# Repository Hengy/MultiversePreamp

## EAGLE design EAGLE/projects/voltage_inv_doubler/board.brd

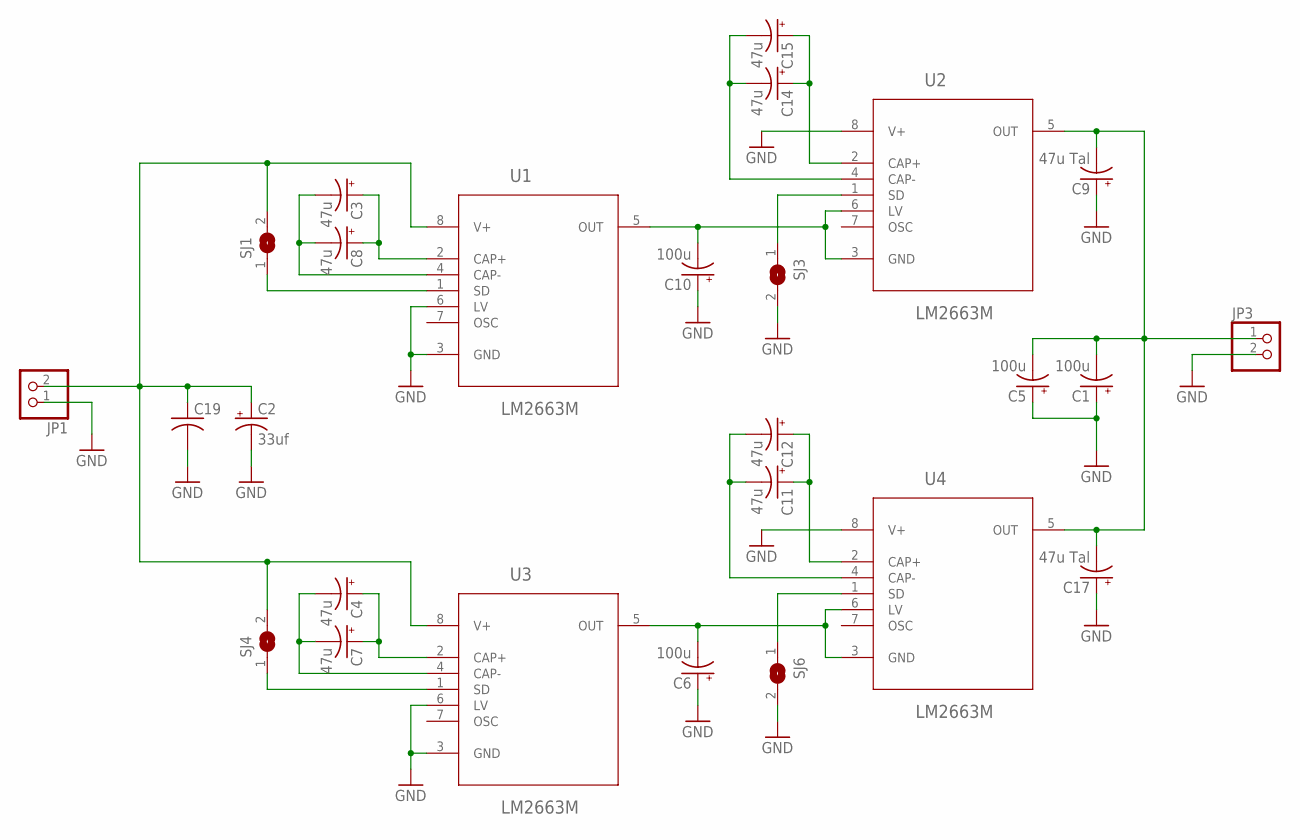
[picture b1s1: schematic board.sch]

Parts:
C1, C5: 100u; E2,5-6
C2: 33uf; E2-5
C3, C4, C7, C8, C11, C12, C14, C15: 47u; EIA3528-KIT
C6, C10: 100u; EIA7343
C9, C17: 47u Tal; EIA6032
C19: C-USC1206; C1206
JP1, JP3: PINHD-1X2; 1X02
SJ1, SJ3, SJ4, SJ6: SJ
U1, U2, U3, U4: LM2663M; SOIC127P620X175-8N

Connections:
GND: C1.+, C2.-, C5.+, C6.A (+), C9.P$1 (+), C10.A (+), C17.P$1 (+), C19.2, JP1.1, JP3.2, SJ3.2, SJ6.2, U1.3 (GND), U1.6 (LV), U2.8 (V+), U3.3 (GND), U3.6 (LV), U4.8 (V+)
unnamed: C2.+, C19.1, JP1.2, SJ1.2, SJ4.2, U1.8 (V+), U3.8 (V+)
unnamed: C14.A (+), C15.A (+), U2.2 (CAP+)
unnamed: SJ1.1, U1.1 (SD)
unnamed: SJ6.1, U4.1 (SD)
unnamed: C3.A (+), C8.A (+), U1.2 (CAP+)
unnamed: C3.C (-), C8.C (-), U1.4 (CAP-)
unnamed: C10.C (-), U1.5 (OUT), U2.3 (GND), U2.6 (LV)
unnamed: C14.C (-), C15.C (-), U2.4 (CAP-)
unnamed: C1.-, C5.-, C9.P$2 (-), C17.P$2 (-), JP3.1, U2.5 (OUT), U4.5 (OUT)
unnamed: SJ3.1, U2.1 (SD)
unnamed: C4.A (+), C7.A (+), U3.2 (CAP+)
unnamed: C4.C (-), C7.C (-), U3.4 (CAP-)
unnamed: C6.C (-), U3.5 (OUT), U4.3 (GND), U4.6 (LV)
unnamed: SJ4.1, U3.1 (SD)
unnamed: C11.A (+), C12.A (+), U4.2 (CAP+)
unnamed: C11.C (-), C12.C (-), U4.4 (CAP-)

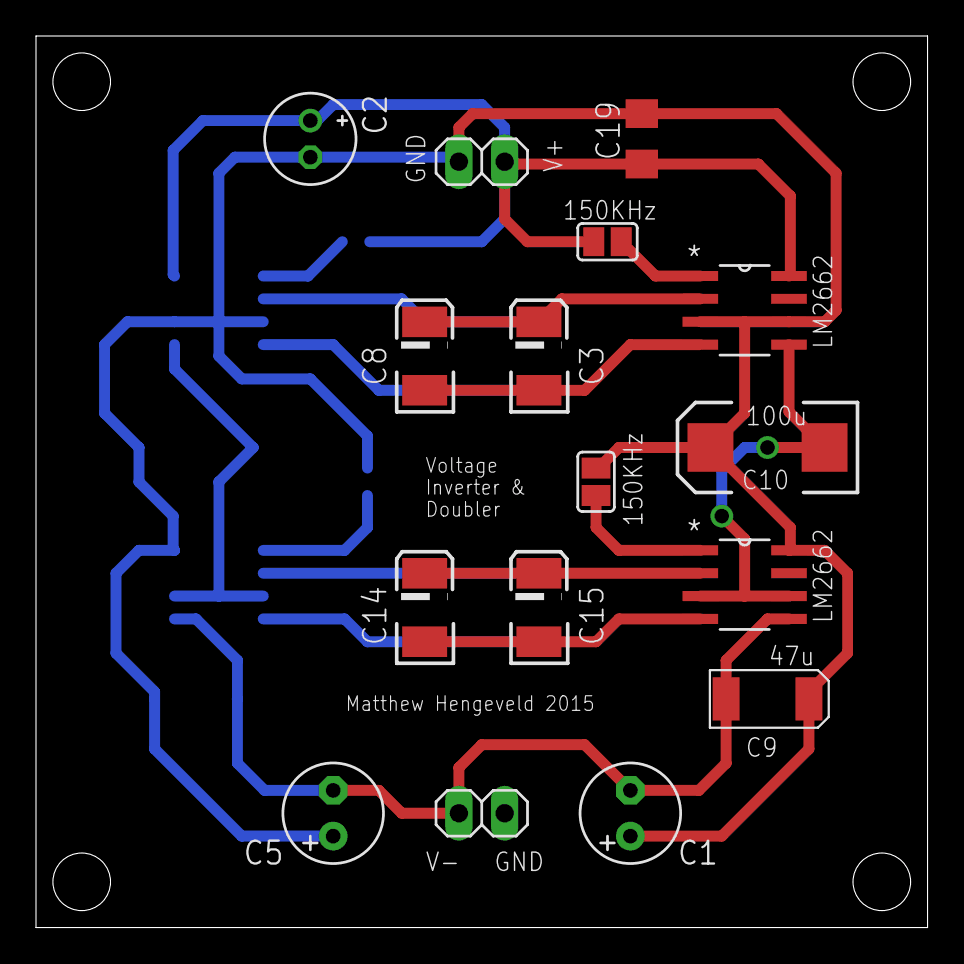
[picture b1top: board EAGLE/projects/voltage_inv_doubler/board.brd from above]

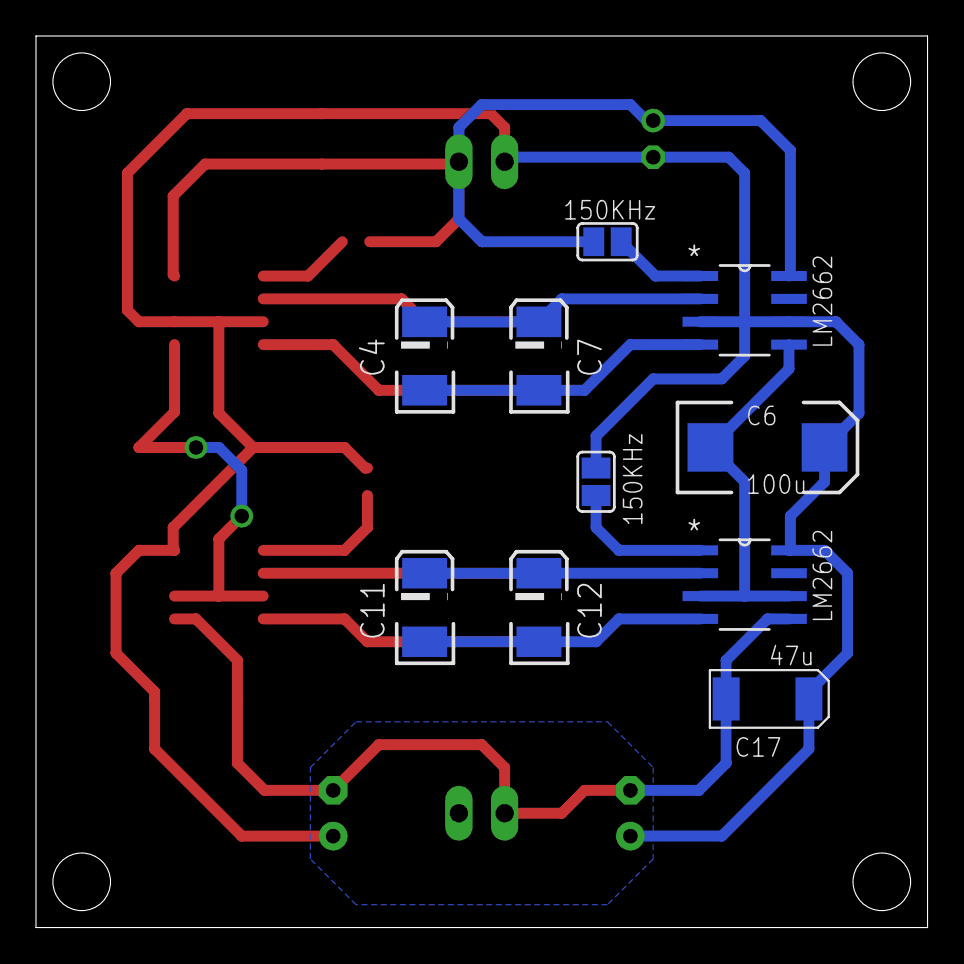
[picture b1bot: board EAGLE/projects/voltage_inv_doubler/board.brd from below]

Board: 2 copper layers, 49.5 x 49.5 mm, 26 parts (10 on the bottom side), 17 nets.

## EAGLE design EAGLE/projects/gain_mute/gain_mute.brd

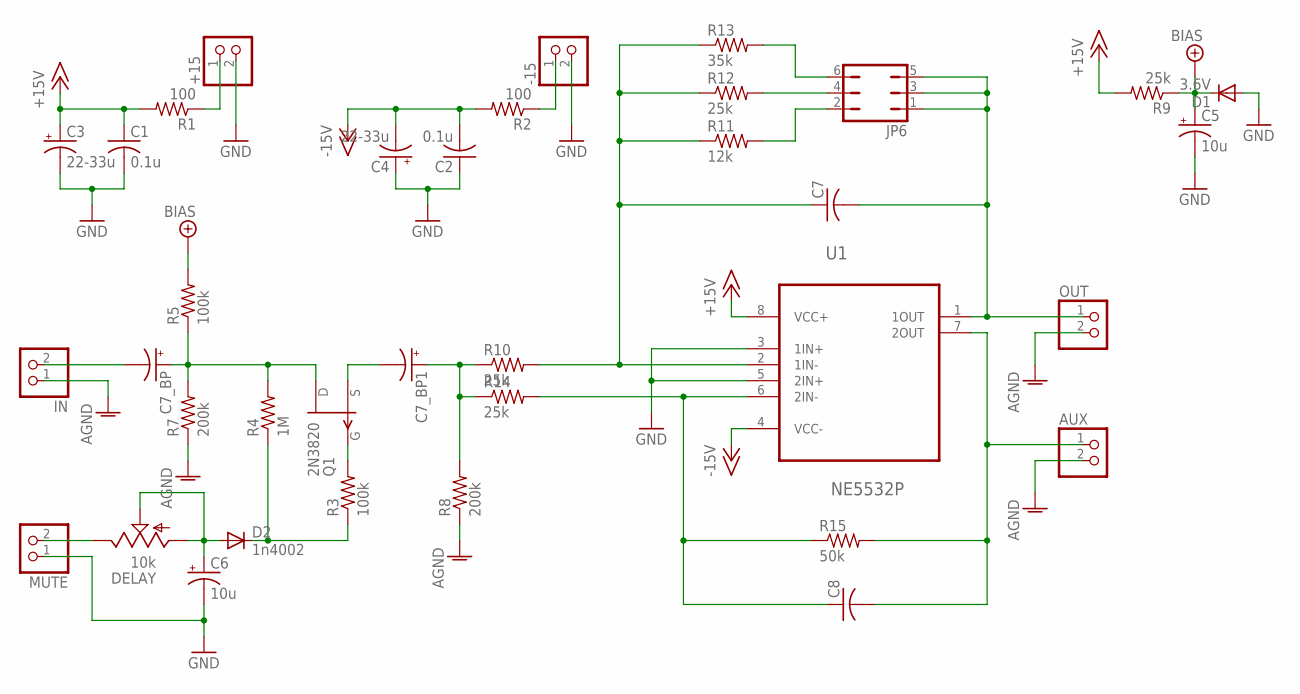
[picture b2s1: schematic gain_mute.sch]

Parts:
+15: PINHD-1X2; 1X02
-15: PINHD-1X2; 1X02
AUX: PINHD-1X2; 1X02
C1, C2: 0.1u; C1206
C3, C4: 22-33u; E2-5
C5, C6: 10u; E2-5
C7, C8: C-US050-024X044; C050-024X044
C7_BP, C7_BP1: CPOL-USE2.5-7; E2,5-7
D1: 3.6V; SOD123
D2: 1n4002; SOD123
DELAY: 10k; 3223J
IN: PINHD-1X2; 1X02
JP6: JP3Q
MUTE: PINHD-1X2; 1X02
OUT: PINHD-1X2; 1X02
Q1: 2N3820; TO92
R1, R2: 100; 0207/7
R3, R5: 100k; R1206
R4: 1M; R1206
R7, R8: 200k; R1206
R9: 25k; R1206
R10, R12, R14: 25k; 0207/7
R11: 12k; 0207/7
R13: 35k; 0207/7
R15: 50k; 0207/7
U1: NE5532P; DIP254P762X508-8

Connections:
+5V/2: C5.+, D1.C, R5.2, R9.1
+15V: C1.1, C3.+, R1.2, R9.2, U1.8 (VCC+)
-15V: C2.2, C4.-, R2.2, U1.4 (VCC-)
AGND: AUX.2, IN.1, OUT.2, R7.1, R8.1
GND: +15.2, -15.2, C1.2, C2.1, C3.-, C4.+, C5.-, C6.-, D1.A, MUTE.1, U1.3 (1IN+), U1.5 (2IN+)
unnamed: +15.1, R1.1
unnamed: C7_BP.-, IN.2
unnamed: DELAY.3 (E), MUTE.2
unnamed: -15.1, R2.1
unnamed: C7_BP.+, Q1.3 (D), R4.2, R5.1, R7.2
unnamed: C6.+, D2.A, DELAY.1 (A), DELAY.2 (S)
unnamed: D2.C, R3.1, R4.1
unnamed: Q1.2 (G), R3.2
unnamed: C7_BP1.-, Q1.1 (S)
unnamed: C7_BP1.+, R8.2, R10.1, R14.1
unnamed: C7.1, R10.2, R11.1, R12.1, R13.1, U1.2 (1IN-)
unnamed: JP6.4, R12.2
unnamed: JP6.6, R13.2
unnamed: JP6.2, R11.2
unnamed: C7.2, JP6.1, JP6.3, JP6.5, OUT.1, U1.1 (1OUT)
unnamed: AUX.1, C8.2, R15.2, U1.7 (2OUT)
unnamed: C8.1, R14.2, R15.1, U1.6 (2IN-)

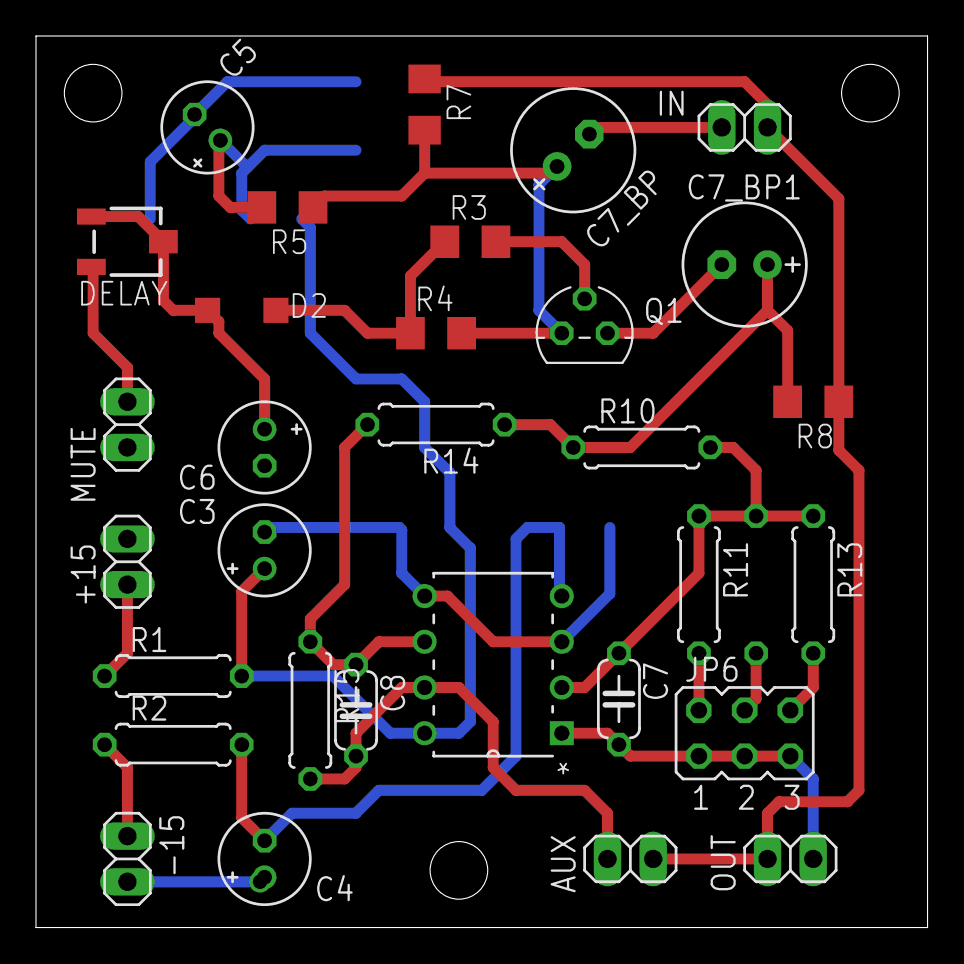
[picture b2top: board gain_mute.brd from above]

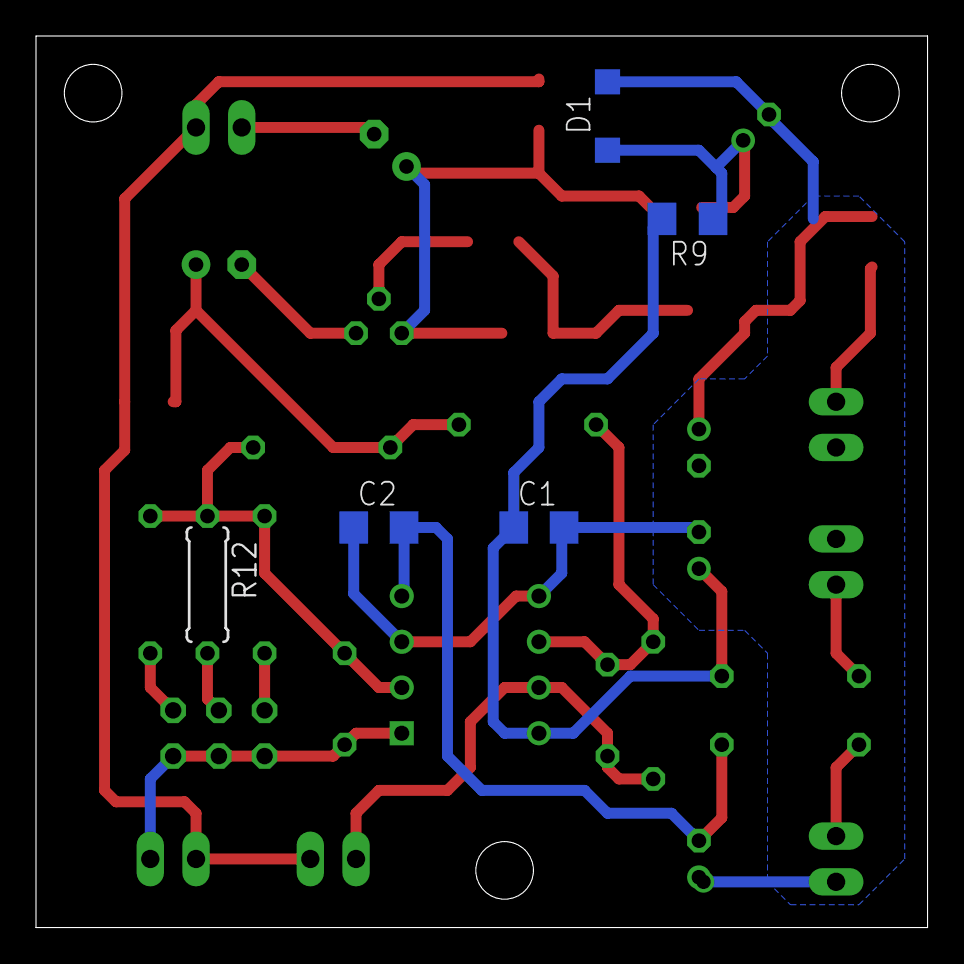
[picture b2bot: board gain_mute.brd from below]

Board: 2 copper layers, 49.5 x 49.5 mm, 36 parts (5 on the bottom side), 22 nets.

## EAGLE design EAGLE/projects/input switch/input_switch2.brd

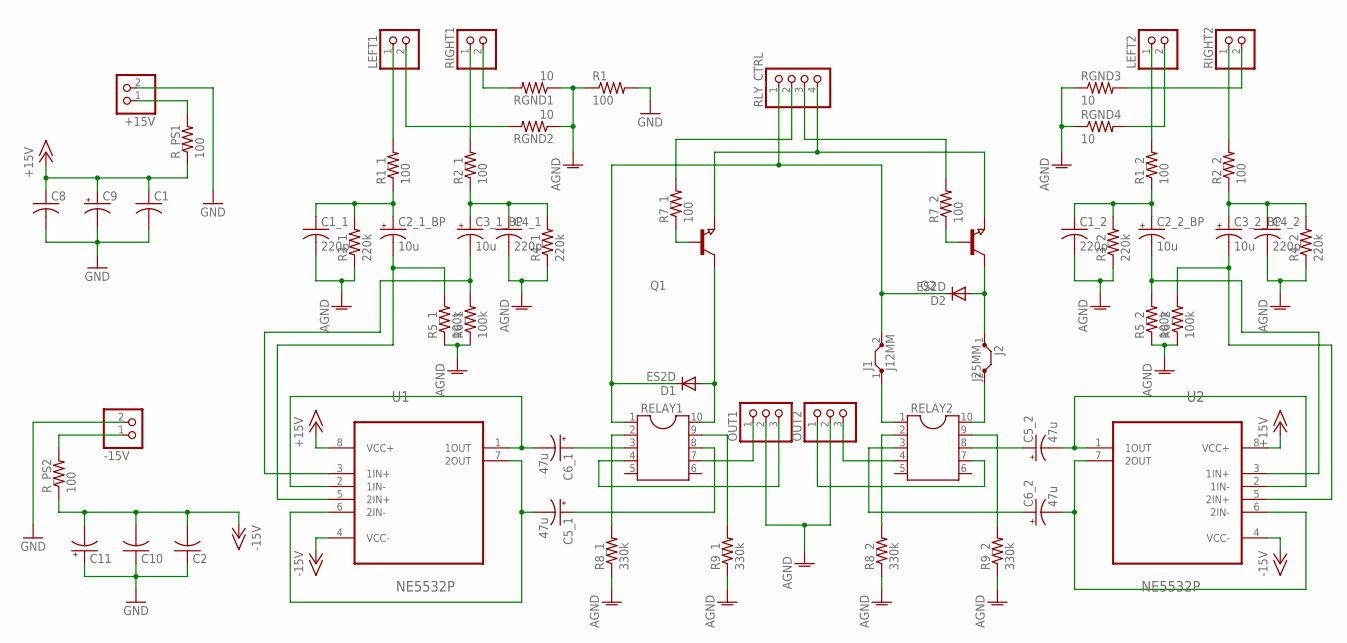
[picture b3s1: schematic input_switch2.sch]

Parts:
+15V: PINHD-1X2; 1X02
-15V: PINHD-1X2; 1X02
C1, C2, C8, C10: C-USC1206; C1206
C1_1, C1_2, C4_1, C4_2: 220p; C025-024X044
C2_1_BP, C2_2_BP, C3_1_BP, C3_2_BP: 10u; E2,5-7
C5_1, C5_2, C6_1, C6_2: 47u; E2-5
C9, C11: CPOL-USE2-5; E2-5
D1, D2: ES2D; SMB
J1: J12MM; 12
J2: J25MM; 25
LEFT1, LEFT2: PINHD-1X2; 1X02
OUT1, OUT2: PINHD-1X3; 1X03
Q1, Q2: NPN-TRANSISTOR_SOT23; SOT23
R1, R7_1, R7_2: 100; R1206
R1_1, R1_2, R2_1, R2_2: 100; 0207/7
R3_1, R3_2, R4_1, R4_2: 220k; 0207/7
R5_1, R5_2, R6_1, R6_2: 100k; 0207/7
R8_1, R8_2, R9_1, R9_2: 330k; R1206
RELAY1, RELAY2: DIL10
RGND1, RGND2, RGND3, RGND4: 10; R1206
RIGHT1, RIGHT2: PINHD-1X2; 1X02
RLY_CTRL: PINHD-1X4; 1X04
R_PS1, R_PS2: 100; 0207/7
U1, U2: NE5532P; DIP254P762X508-8

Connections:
+15V: C1.1, C8.1, C9.+, R_PS1.1, U1.8 (VCC+), U2.8 (VCC+)
-15V: C2.2, C10.2, C11.-, R_PS2.1, U1.4 (VCC-), U2.4 (VCC-)
AGND: C1_1.2, C1_2.2, C4_1.2, C4_2.2, OUT1.2, OUT2.2, R1.1, R3_1.1, R3_2.1, R4_1.1, R4_2.1, R5_1.1, R5_2.1, R6_1.1, R6_2.1, R8_1.1, R8_2.1, R9_1.1, R9_2.1, RGND1.1, RGND2.1, RGND3.1, RGND4.1
GND: +15V.2, -15V.2, C1.2, C2.1, C8.2, C9.-, C10.1, C11.+, R1.2
unnamed: R2_1.2, RIGHT1.1
unnamed: LEFT1.1, R1_1.2
unnamed: C1_1.1, C2_1_BP.+, R1_1.1, R3_1.2
unnamed: C2_1_BP.-, R5_1.2, U1.5 (2IN+)
unnamed: C5_1.-, U1.6 (2IN-), U1.7 (2OUT)
unnamed: C3_1_BP.+, C4_1.1, R2_1.1, R4_1.2
unnamed: C6_1.-, U1.1 (1OUT), U1.2 (1IN-)
unnamed: C6_1.+, RELAY1.3
unnamed: OUT1.3, RELAY1.4
unnamed: C6_2.-, U2.6 (2IN-), U2.7 (2OUT)
unnamed: R8_1.2, RELAY1.2
unnamed: R9_1.2, RELAY1.9
unnamed: C5_2.-, U2.1 (1OUT), U2.2 (1IN-)
unnamed: OUT1.1, RELAY1.7
unnamed: R7_1.2, RLY_CTRL.2
unnamed: Q1.1 (B), R7_1.1
unnamed: -15V.1, R_PS2.2
unnamed: D1.A, Q1.3 (C), RELAY1.10
unnamed: OUT2.1, RELAY2.7
unnamed: C3_1_BP.-, R6_1.2, U1.3 (1IN+)
unnamed: R2_2.2, RIGHT2.1
unnamed: LEFT2.1, R1_2.2
unnamed: C1_2.1, C2_2_BP.+, R1_2.1, R3_2.2
unnamed: C3_2_BP.+, C4_2.1, R2_2.1, R4_2.2
unnamed: +15V.1, R_PS1.2
unnamed: C3_2_BP.-, R6_2.2, U2.5 (2IN+)
unnamed: C2_2_BP.-, R5_2.2, U2.3 (1IN+)
unnamed: OUT2.3, RELAY2.4
unnamed: C6_2.+, RELAY2.3
unnamed: C5_2.+, RELAY2.8
unnamed: C5_1.+, RELAY1.8
unnamed: R7_2.2, RLY_CTRL.3
unnamed: LEFT1.2, RGND2.2
unnamed: R8_2.2, RELAY2.2
unnamed: R9_2.2, RELAY2.9
unnamed: RGND1.2, RIGHT1.2
unnamed: D1.C, D2.C, J1.2, RELAY1.1, RLY_CTRL.1
unnamed: D2.A, J2.1, Q2.3 (C)
unnamed: Q2.1 (B), R7_2.1
unnamed: Q1.2 (E), Q2.2 (E), RLY_CTRL.4
unnamed: J1.1, RELAY2.1
unnamed: RGND3.2, RIGHT2.2
unnamed: LEFT2.2, RGND4.2
unnamed: J2.2, RELAY2.10

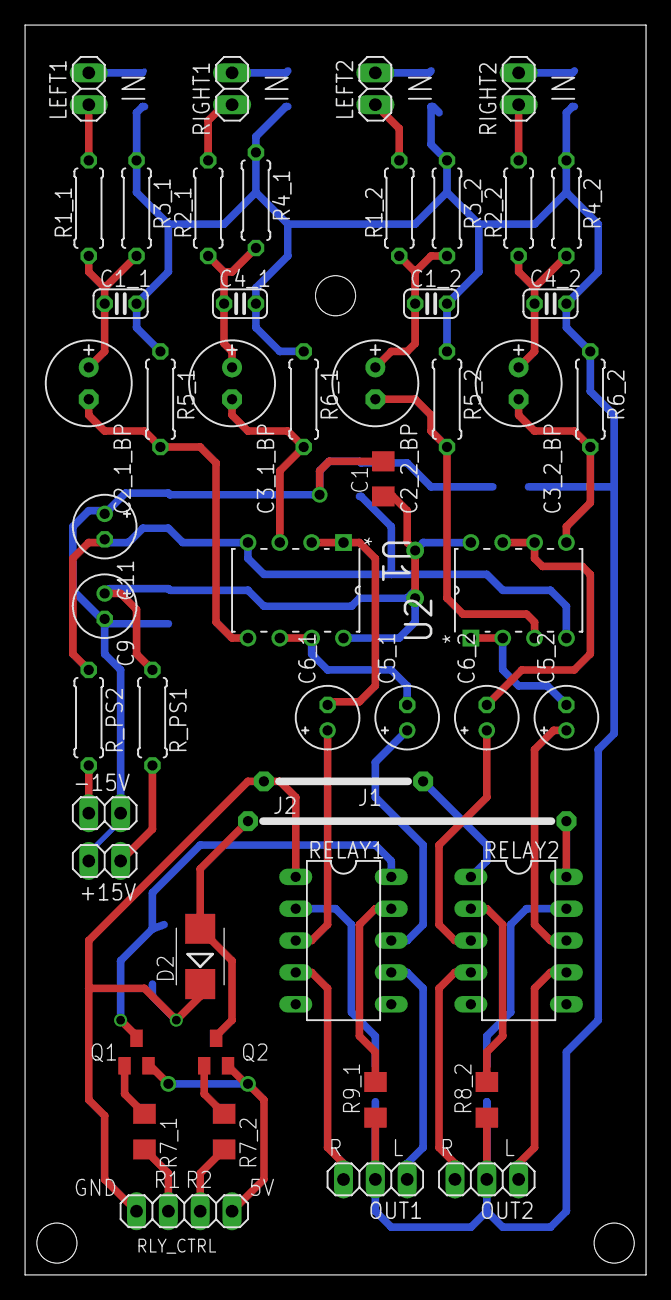
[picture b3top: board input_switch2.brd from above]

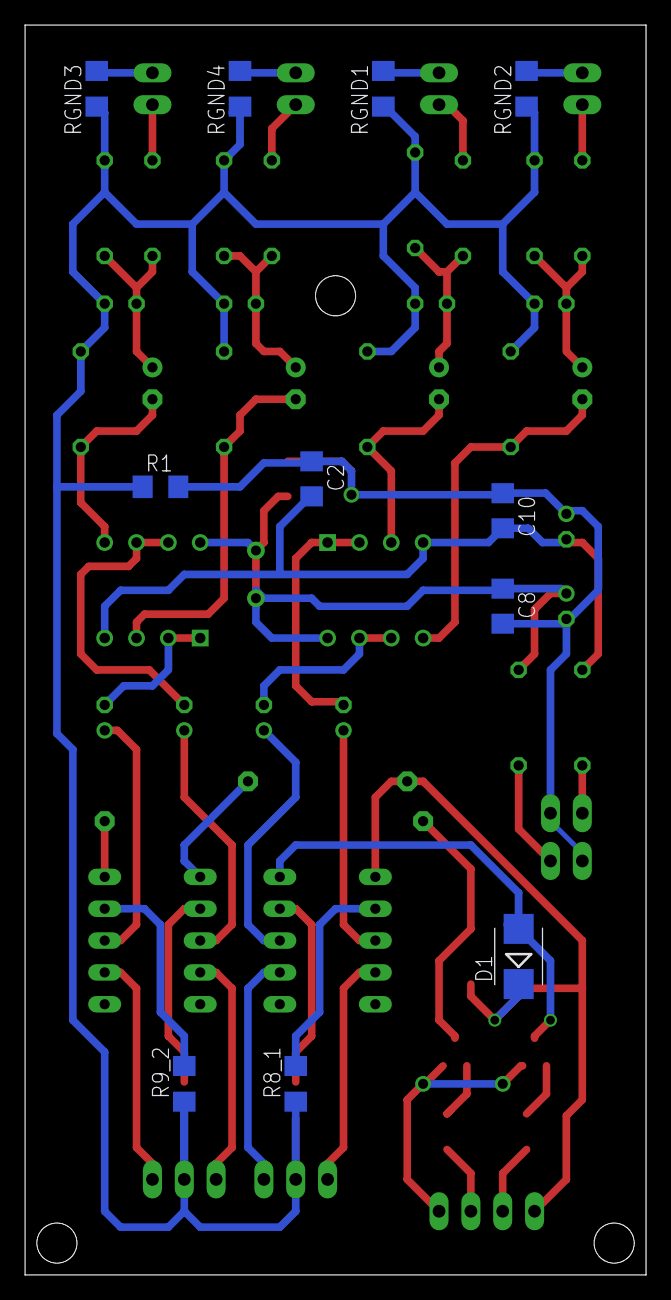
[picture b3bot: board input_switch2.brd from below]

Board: 2 copper layers, 49.5 x 99.7 mm, 62 parts (11 on the bottom side), 48 nets.

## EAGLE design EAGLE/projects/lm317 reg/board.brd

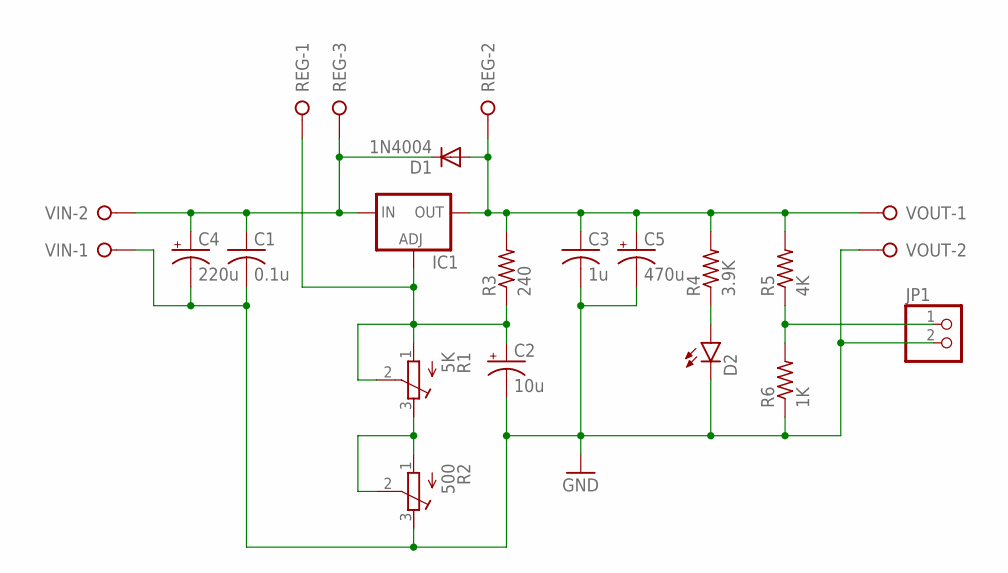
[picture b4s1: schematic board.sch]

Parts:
C1: 0.1u; C1206
C2: 10u; E2-5
C3: 1u; C1206
C4: 220u; E5-10,5
C5: 470u; E5-13
D1: 1N4004; DO41-10
D2: LED1206; LED-1206
IC1: LM317TS; 317TS
JP1: PINHD-1X2; 1X02
R1: 5K; RTRIM3296W
R2: 500; RTRIM3296W
R3: 240; 0309/10
R4: 3.9K; R1206
R5: 4K; R1206
R6: 1K; R1206
REG: W237-3E
VIN: W237-02P; W237-132
VOUT: W237-02P; W237-132

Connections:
GND: C1.2, C2.-, C3.2, C4.-, C5.-, D2.C, JP1.2, R2.3 (E), R6.1, VIN.1, VOUT.2
unnamed: C1.1, C4.+, D1.C, IC1.3 (IN), REG.3, VIN.2
unnamed: D2.A, R4.1
unnamed: C2.+, IC1.1 (ADJ), R1.1 (A), R1.2 (S), R3.1, REG.1
unnamed: R1.3 (E), R2.1 (A), R2.2 (S)
unnamed: JP1.1, R5.1, R6.2
unnamed: C3.1, C5.+, D1.A, IC1.2 (OUT), R3.2, R4.2, R5.2, REG.2, VOUT.1

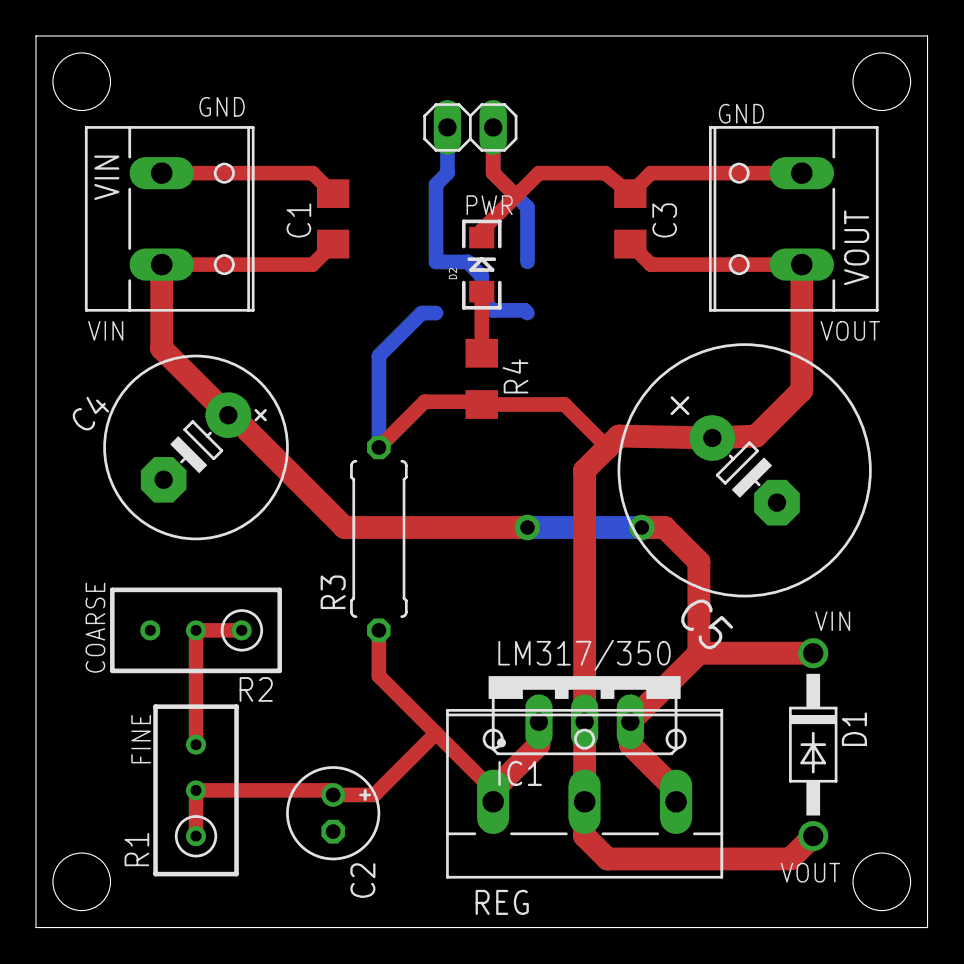
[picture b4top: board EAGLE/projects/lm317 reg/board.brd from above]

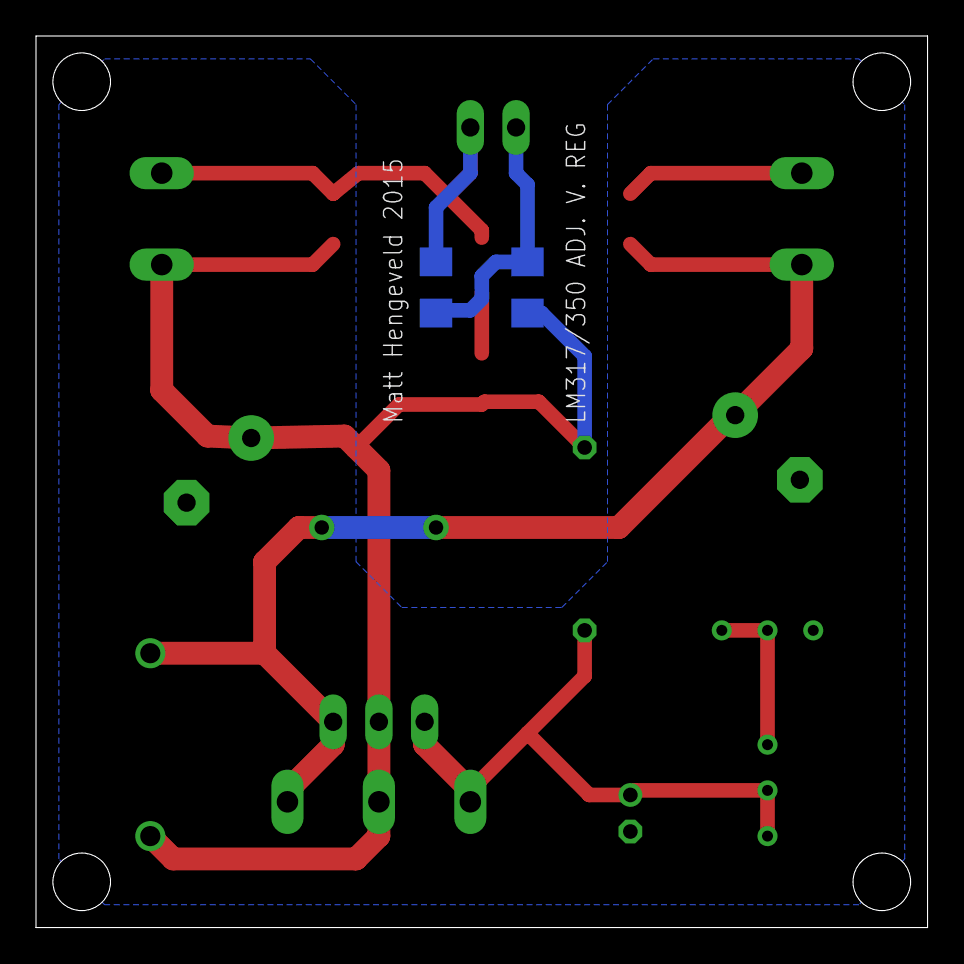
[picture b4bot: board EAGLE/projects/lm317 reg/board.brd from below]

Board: 2 copper layers, 49.5 x 49.5 mm, 18 parts (2 on the bottom side), 7 nets.

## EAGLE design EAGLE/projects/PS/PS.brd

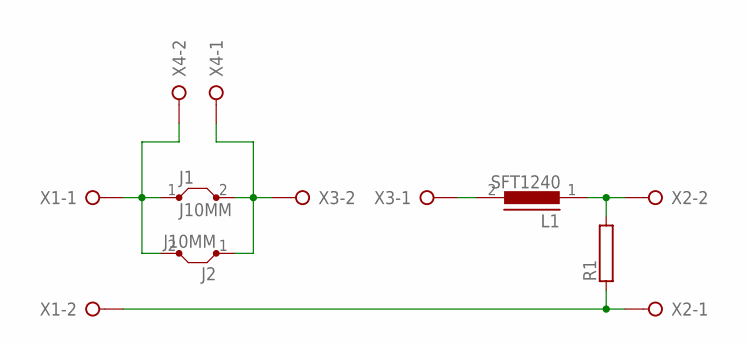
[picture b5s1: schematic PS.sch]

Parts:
J1, J2: J10MM; 10
L1: SFT1240
R1: RAC04; AC04
X1, X2, X3, X4: W237-02P; W237-132

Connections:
GND: R1.1, X1.2, X2.1
unnamed: J1.2, J2.1, X3.2, X4.1
VCAPS: L1.2, X3.1
VIN: J1.1, J2.2, X1.1, X4.2
VOUT: L1.1, R1.2, X2.2

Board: 2 copper layers, 8 parts (0 on the bottom side), 5 nets, no tracks yet.

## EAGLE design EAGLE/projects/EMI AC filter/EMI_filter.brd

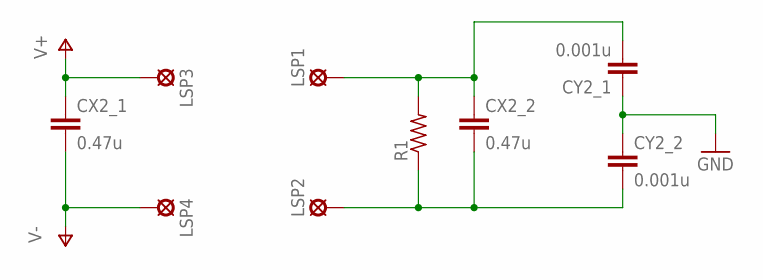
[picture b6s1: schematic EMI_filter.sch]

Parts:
CX2_1, CX2_2: 0.47u; C150-091X182
CY2_1, CY2_2: 0.001u; C102-043X133
LSP1, LSP2, LSP3, LSP4: SE14
R1: R-US_0617/22; 0617/22

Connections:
GND: CY2_1.1, CY2_2.1
unnamed: CX2_2.1, CY2_1.2, LSP1.MP, R1.2
unnamed: CX2_2.2, CY2_2.2, LSP2.MP, R1.1
V+: CX2_1.1, LSP3.MP
V-: CX2_1.2, LSP4.MP

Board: 2 copper layers, 9 parts (0 on the bottom side), 5 nets, no tracks yet.

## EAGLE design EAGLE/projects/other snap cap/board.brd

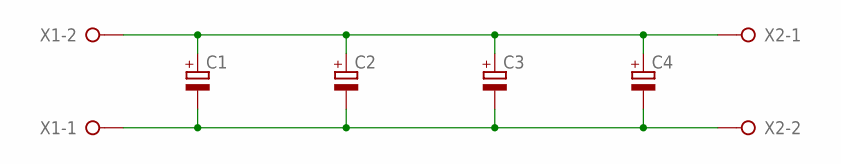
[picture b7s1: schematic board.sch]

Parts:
C1: CPOL-EUE10-30; EB30D
C2, C3, C4: CPOL-EUE10-22.5; EB22,5D
X1, X2: W237-02P; W237-132

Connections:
GND: C1.-, C2.-, C3.-, C4.-, X1.1, X2.2
V+: C1.+, C2.+, C3.+, C4.+, X1.2, X2.1

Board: 2 copper layers, 6 parts (0 on the bottom side), 2 nets, no tracks yet.

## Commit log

2015-01-07 :lollipop: Added .gitattributes
2015-01-09 added
2015-04-10 ChargePump
2015-04-15 Power Supply
2015-04-15 Power Supply and EMI filter
2015-04-17 PS boards
2015-04-17 stuff
2015-04-18 Input Switch
2015-04-18 DIP NE5532
2015-04-21 input
2015-04-21 Input Board done
2015-04-22 regulator
2015-04-22 LM317 Reg
2015-05-02 a lot
2015-06-24 V_invert_double fixes

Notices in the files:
parts and their libraries:
SparkFun-Aesthetics: Licensing: Creative Commons ShareAlike 4.0 International - https://creativecommons.org/licenses/by-sa/4.0
